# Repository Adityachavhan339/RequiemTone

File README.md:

# RequiemTone
RequiemTone is a small electronic instrument that lets you play notes, make little melodies, and create retro video-game sounds.
The idea is to create a simple electronic instrument with eight buttons, two knobs, and a piezo sounder.

The Parts I Am Using:

    -8 physical buttons for playing notes or triggering sounds
    -2 potentiometers for adjusting sound parameters
    -Piezo sound output
    -USB-powered Raspberry Pi Pico
    -Custom-designed PCB
    -Planned custom firmware for generating sounds and melodies

What Its Gonna Do:
The Raspberry Pi Pico reads all buttons as digital inputs and the two potentiometers as analog inputs.
The firmware will use these inputs to generate sound through the piezo sounder.
The buttons will be programmed to play different notes, while the potentiometers can control parameters such as tempo and pitch.

## Why I made it:
Well as always couldn't find better idea and because halfway i found out Mp3 player is not considered an instrument😅.

## Schematic Image:

## PCB Image:

## CAD Images:

( I Am Still Writing Firmware i have no idea how still looking at it and i don't know what else to write in readme so that's it for now thanks i will keep updating it in future)
## AI Disclosure
Well I Heard Somewhere AI Is Shit With hardware and i experienced it firsthand it sucks in this so i did it all by myself

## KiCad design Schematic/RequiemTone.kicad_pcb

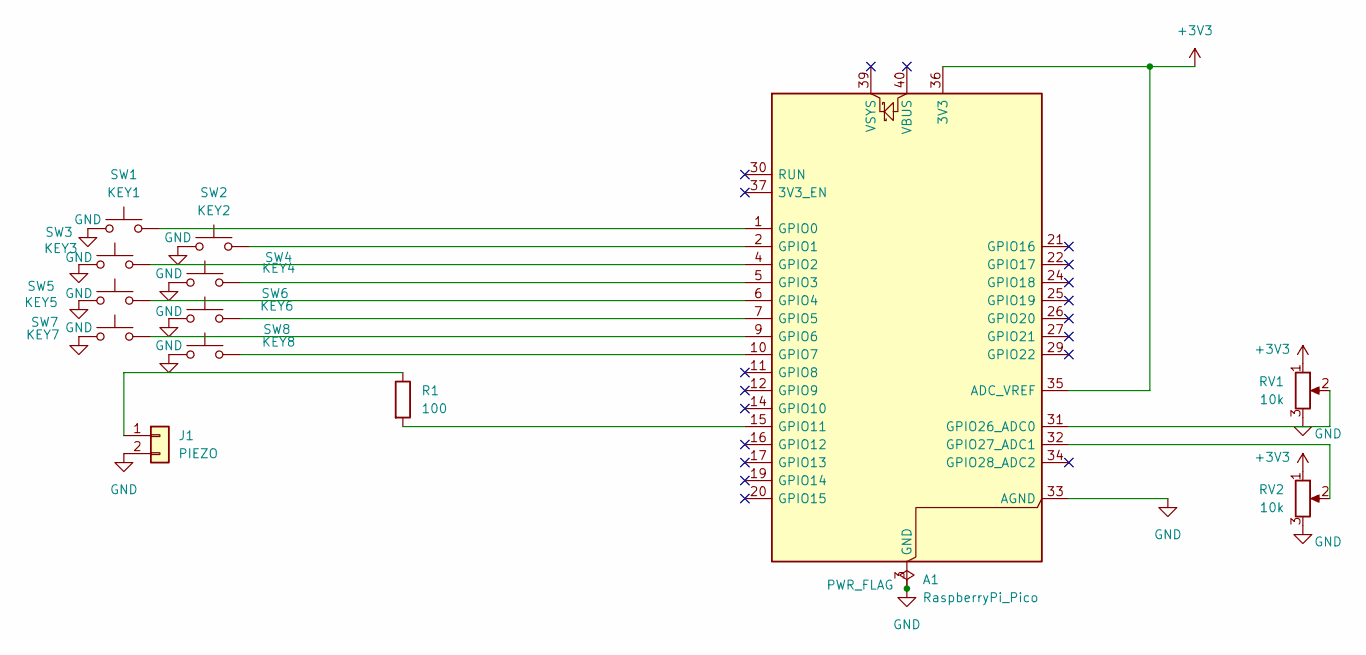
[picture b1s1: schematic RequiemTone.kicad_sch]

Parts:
A1: RaspberryPi_Pico; RaspberryPi_Pico_Common_SMD
J1: PIEZO; PinHeader_1x02_P2.54mm_Vertical
R1: 100; R_Axial_DIN0207_L6.3mm_D2.5mm_P7.62mm_Horizontal
RV1, RV2: 10k; Potentiometer_Alpha_RD901F-40-00D_Single_Vertical
SW1: KEY1; SW_PUSH_6mm
SW2: KEY2; SW_PUSH_6mm
SW3: KEY3; SW_PUSH_6mm
SW4: KEY4; SW_PUSH_6mm
SW5: KEY5; SW_PUSH_6mm
SW6: KEY6; SW_PUSH_6mm
SW7: KEY7; SW_PUSH_6mm
SW8: KEY8; SW_PUSH_6mm

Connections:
+3V3: A1.35 (ADC_VREF), A1.36 (3V3), RV1.1, RV2.1
GND: A1.3 (GND), A1.8 (GND), A1.13 (GND), A1.18 (GND), A1.23 (GND), A1.28 (GND), A1.33 (AGND), A1.38 (GND), J1.2, RV1.3, RV2.3, SW1.1, SW2.1, SW3.1, SW4.1, SW5.1, SW6.1, SW7.1, SW8.1
unnamed: A1.1 (GPIO0), SW1.2
unnamed: A1.2 (GPIO1), SW2.2
unnamed: A1.4 (GPIO2), SW3.2
unnamed: A1.5 (GPIO3), SW4.2
unnamed: A1.6 (GPIO4), SW5.2
unnamed: A1.7 (GPIO5), SW6.2
unnamed: A1.9 (GPIO6), SW7.2
unnamed: A1.10 (GPIO7), SW8.2
unnamed: A1.15 (GPIO11), R1.2
unnamed: A1.31 (GPIO26_ADC0), RV1.2
unnamed: A1.32 (GPIO27_ADC1), RV2.2
unnamed: J1.1, R1.1

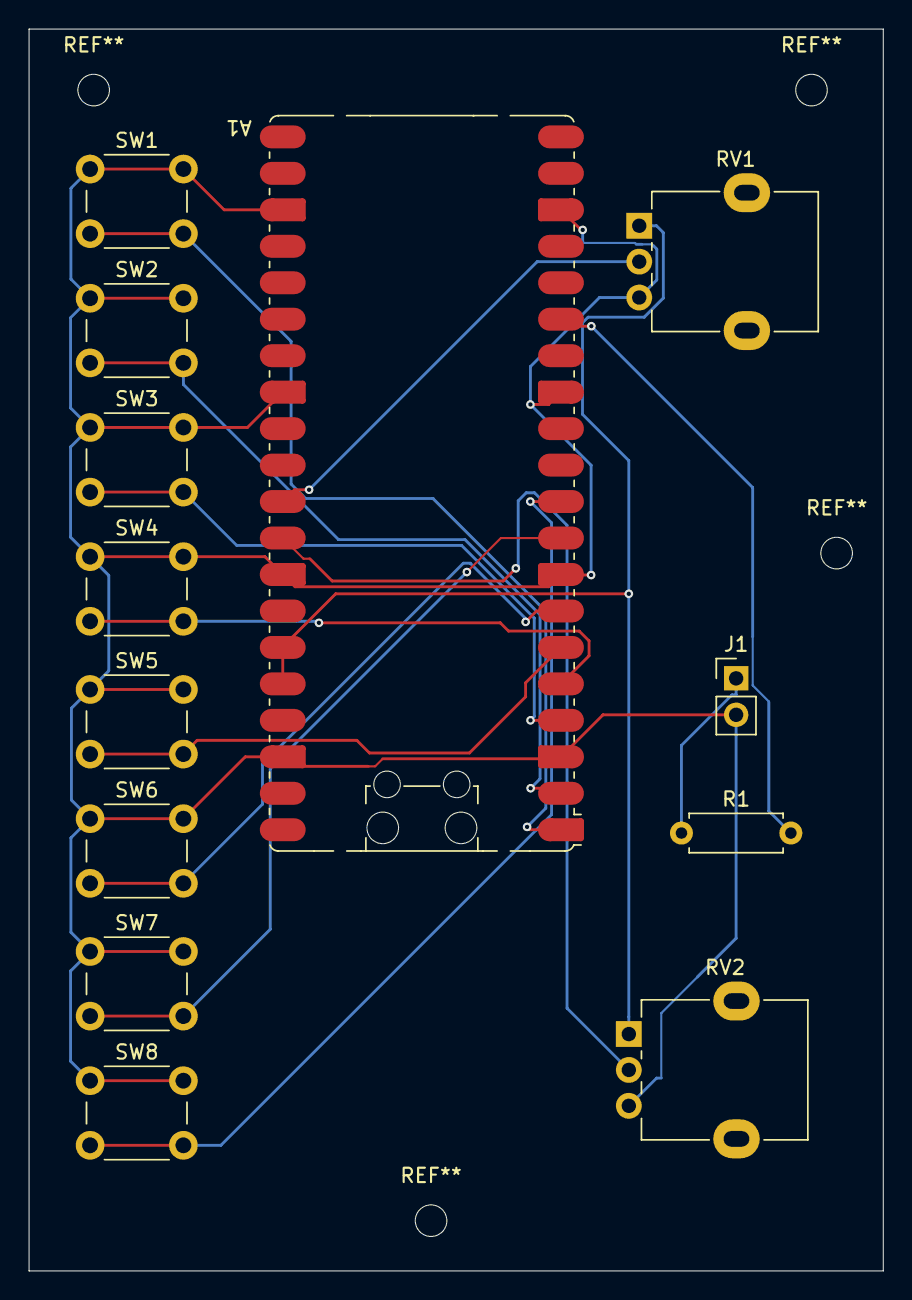
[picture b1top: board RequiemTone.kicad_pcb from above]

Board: 2 copper layers, 59.5 x 86.5 mm, 13 parts (0 on the bottom side), 14 nets.
